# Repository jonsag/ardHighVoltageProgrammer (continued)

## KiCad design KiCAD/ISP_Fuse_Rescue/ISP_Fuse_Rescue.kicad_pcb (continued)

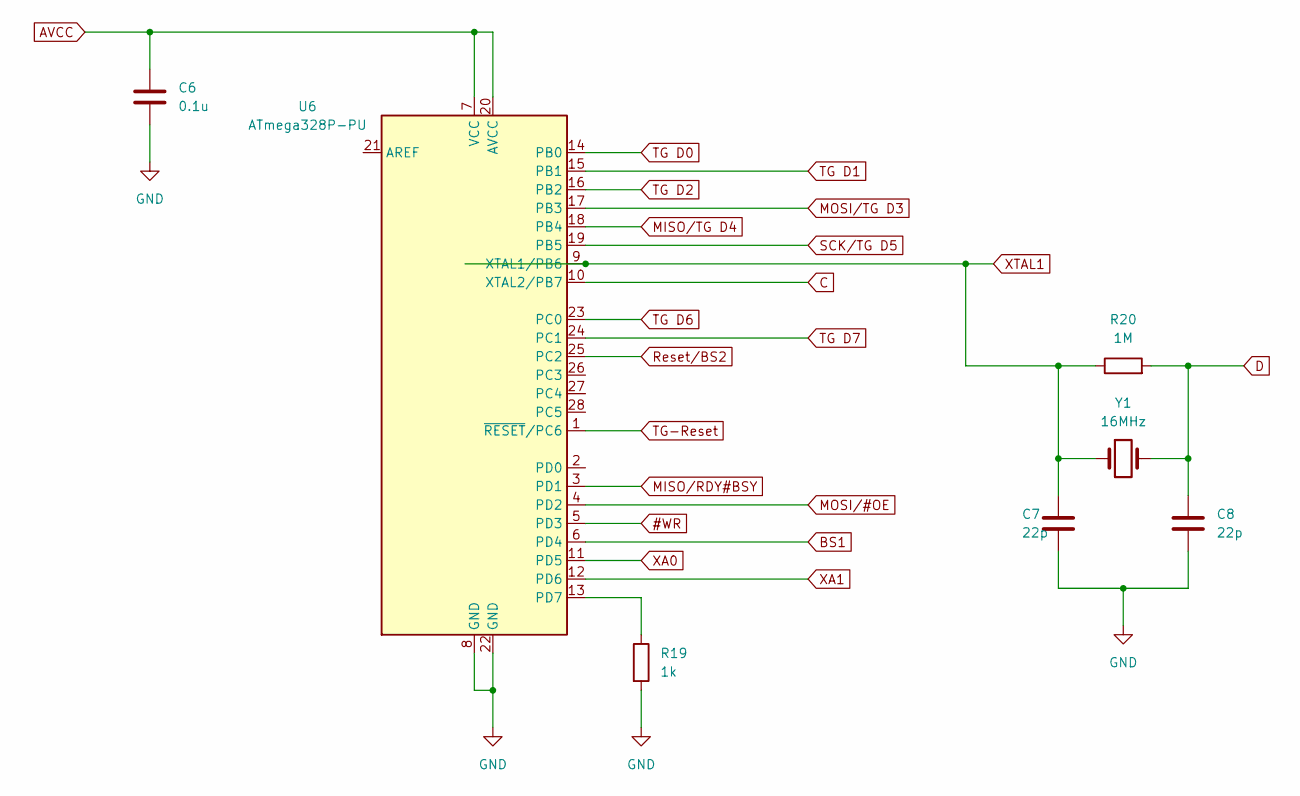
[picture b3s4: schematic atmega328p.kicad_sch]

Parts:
C6: 0.1u; CP_Radial_D5.0mm_P2.50mm_larger_pads
C7, C8: 22p; C_Disc_D3.0mm_W1.6mm_P2.50mm_larg
R19: 1k; R_Axial_DIN0207_L6.3mm_D2.5mm_P10.16mm_Horizontal_large
R20: 1M; R_Axial_DIN0207_L6.3mm_D2.5mm_P10.16mm_Horizontal_large
U6: ATmega328P-PU; ZIF_DIP_Socket-28_W6.9_W7.62_W7.62_W12.7_W13.5_large
Y1: 16MHz; Crystal_HC49-4H_Vertical_large

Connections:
#WR: U6.5 (PD3); also elsewhere on the board
AVCC: C6.1, U6.7 (VCC), U6.20 (AVCC); also elsewhere on the board
BS1: U6.6 (PD4); also elsewhere on the board
C: U6.10 (XTAL2/PB7); also elsewhere on the board
D: C8.1, R20.2, Y1.2; also elsewhere on the board
GND: C6.2, C7.2, C8.2, R19.2, U6.8 (GND), U6.22 (GND); also elsewhere on the board
MISO/RDY#BSY: U6.3 (PD1); also elsewhere on the board
MISO/TG D4: U6.18 (PB4); also elsewhere on the board
MOSI/#OE: U6.4 (PD2); also elsewhere on the board
MOSI/TG D3: U6.17 (PB3); also elsewhere on the board
unnamed: R19.1, U6.13 (PD7)
Reset/BS2: U6.25 (PC2); also elsewhere on the board
SCK/TG D5: U6.19 (PB5); also elsewhere on the board
TG D0: U6.14 (PB0); also elsewhere on the board
TG D1: U6.15 (PB1); also elsewhere on the board
TG D2: U6.16 (PB2); also elsewhere on the board
TG D6: U6.23 (PC0); also elsewhere on the board
TG D7: U6.24 (PC1); also elsewhere on the board
TG-Reset: U6.1 (~RESET/PC6); also elsewhere on the board
XA0: U6.11 (PD5)
XA1: U6.12 (PD6); also elsewhere on the board
XTAL1: C7.1, R20.1, U6.9 (XTAL1/PB6), Y1.1; also elsewhere on the board

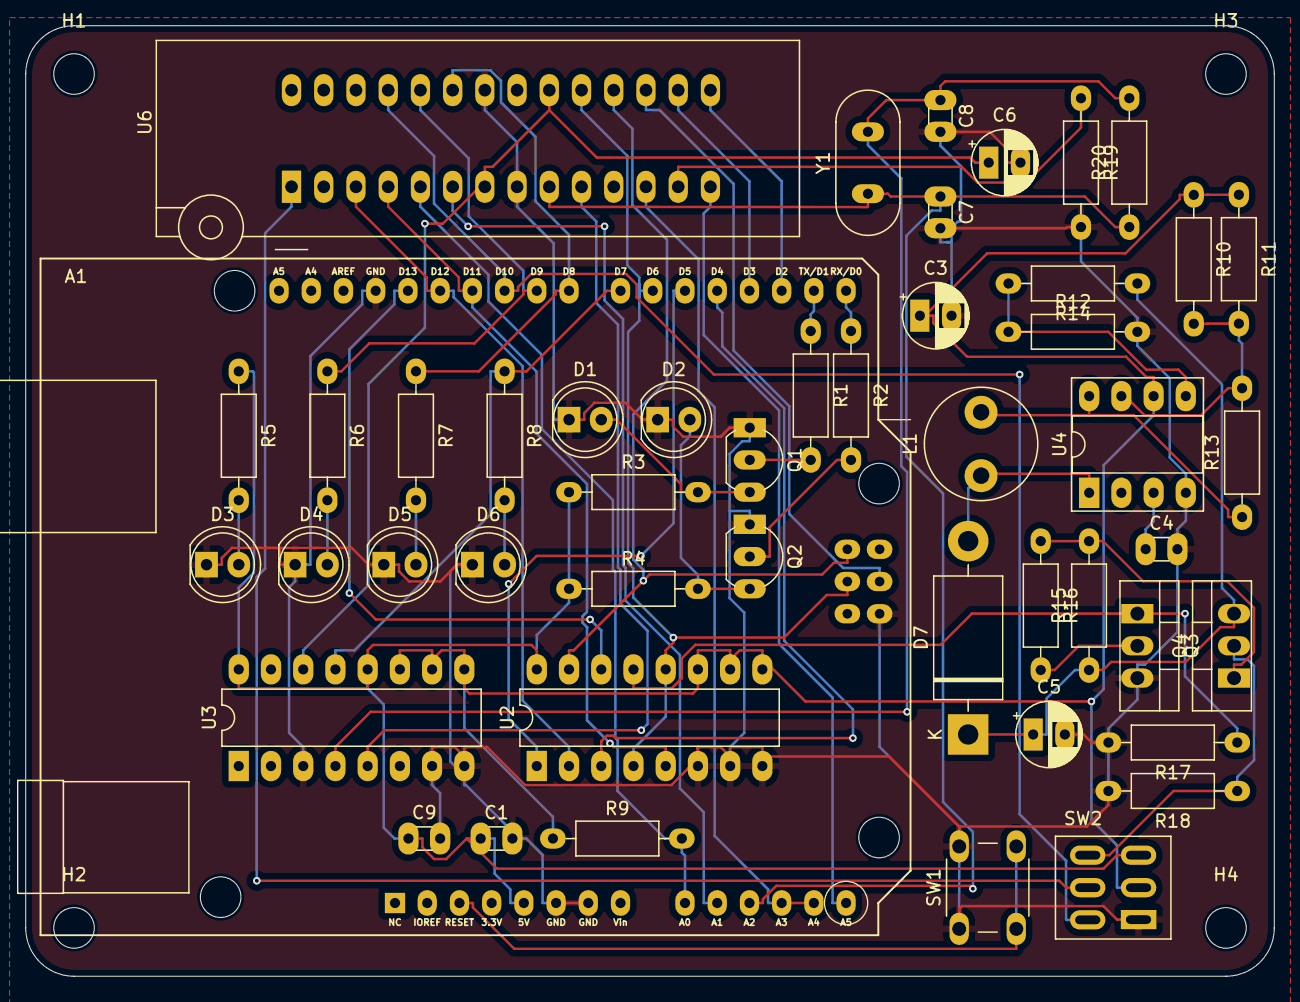
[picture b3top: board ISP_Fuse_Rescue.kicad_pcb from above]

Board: 2 copper layers, 98.4 x 74.9 mm, 52 parts (0 on the bottom side), 48 nets.

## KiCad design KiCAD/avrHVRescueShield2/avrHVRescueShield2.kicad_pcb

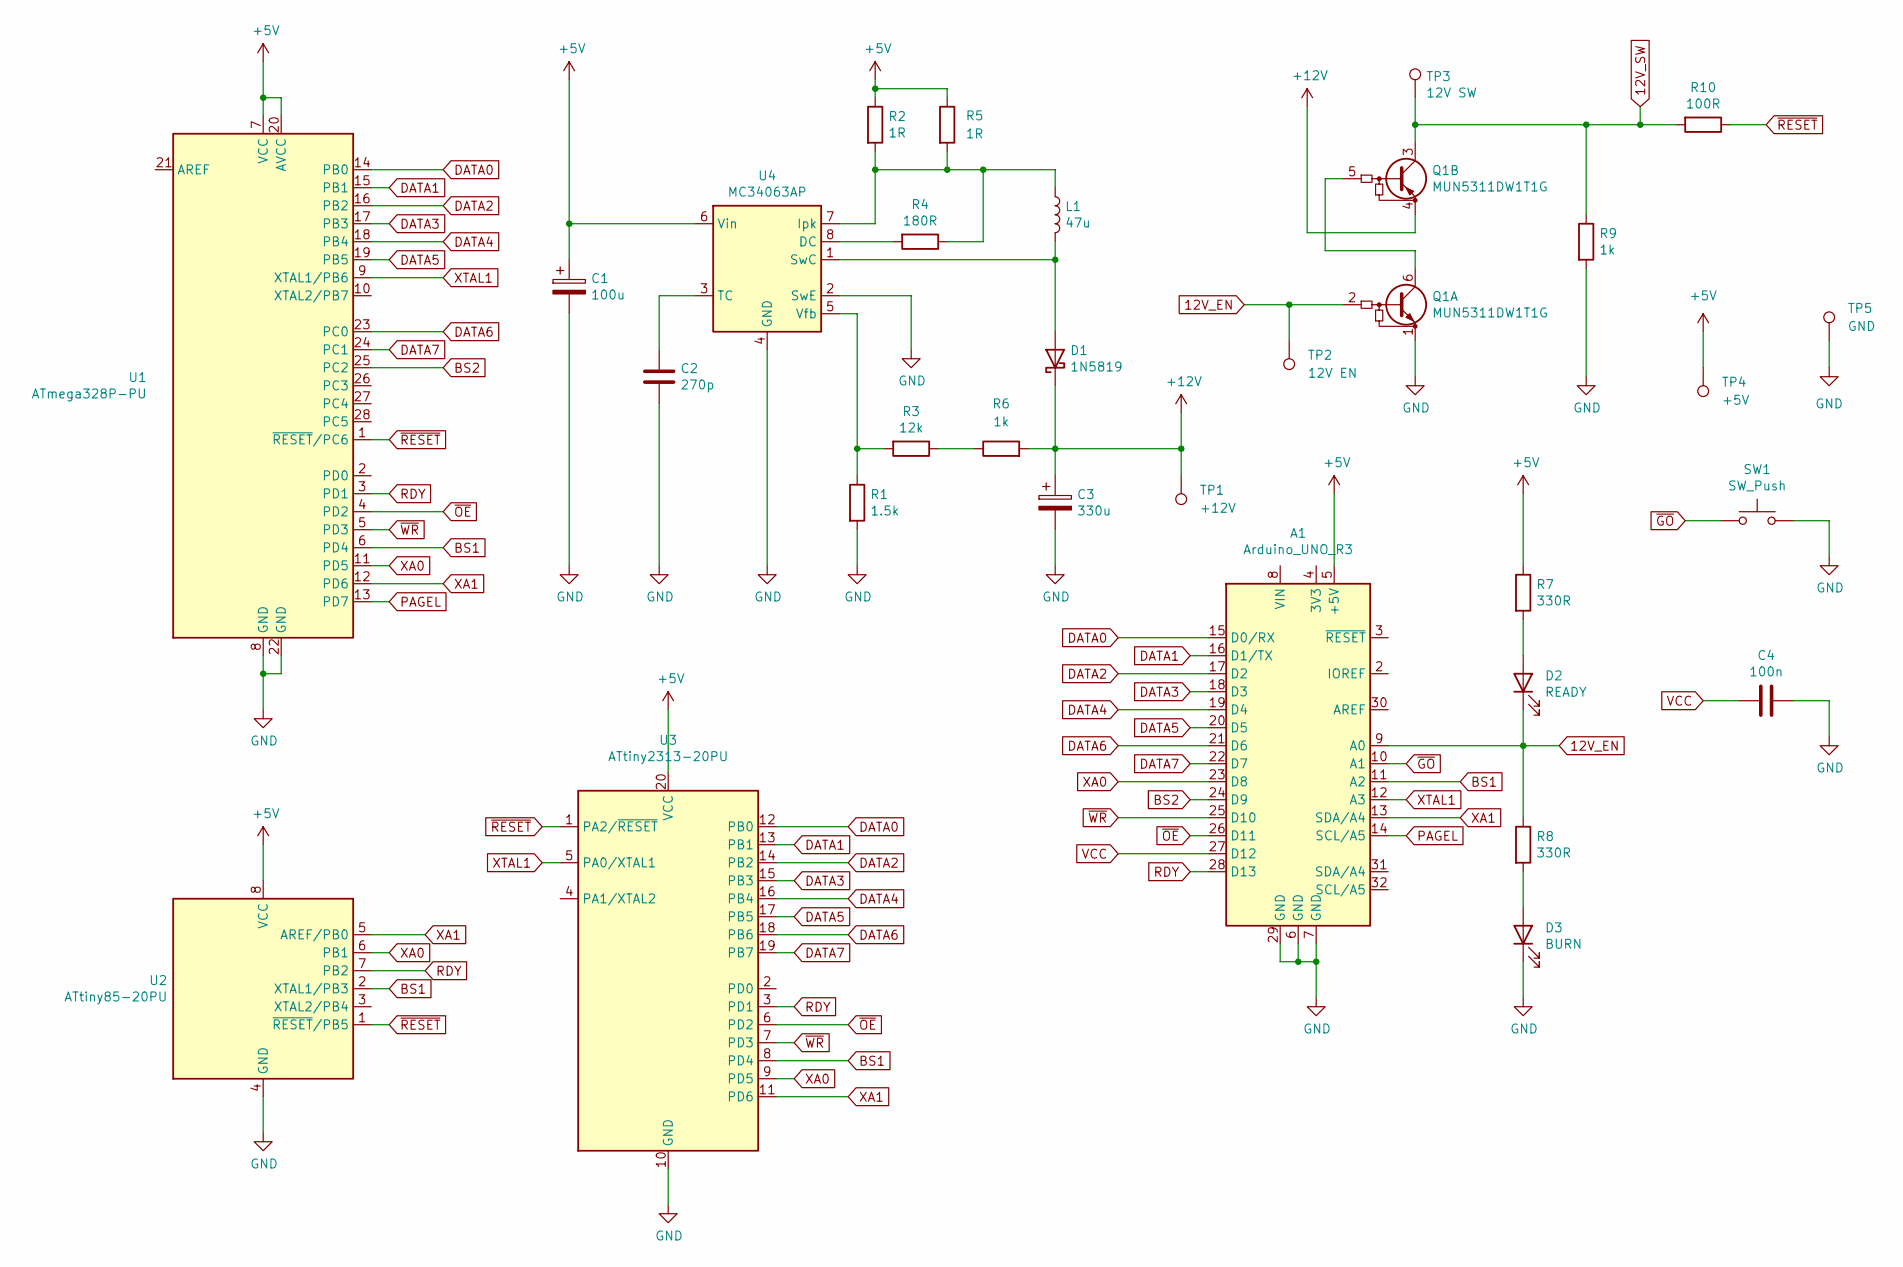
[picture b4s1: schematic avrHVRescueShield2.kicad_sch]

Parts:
A1: Arduino_UNO_R3; Arduino_UNO_R3_shield_large
C1: 100u; CP_Radial_D5.0mm_P2.50mm_larger_pads
C2: 270p; C_Disc_D3.0mm_W1.6mm_P2.50mm_larg
C3: 330u; CP_Radial_D10.0mm_P5.00mm_larger
C4: 100n; C_Disc_D3.0mm_W1.6mm_P2.50mm_larg
D1: 1N5819; D_DO-35_SOD27_P7.62mm_Horizontal_large
D2: READY; LED_D5.0mm_larger_pads
D3: BURN; LED_D5.0mm_larger_pads
L1: 47u; L_Axial_L9.5mm_D4.0mm_P12.70mm_Horizontal_Fastron_SMCC_large
Q1: MUN5311DW1T1G; SOT-363_SC-70-6_Handsoldering
R1: 1.5k; R_Axial_DIN0207_L6.3mm_D2.5mm_P10.16mm_Horizontal_large
R2, R5: 1R; R_Axial_DIN0207_L6.3mm_D2.5mm_P10.16mm_Horizontal_large
R3: 12k; R_Axial_DIN0207_L6.3mm_D2.5mm_P10.16mm_Horizontal_large
R4: 180R; R_Axial_DIN0207_L6.3mm_D2.5mm_P10.16mm_Horizontal_large
R6, R9: 1k; R_Axial_DIN0207_L6.3mm_D2.5mm_P10.16mm_Horizontal_large
R7, R8: 330R; R_Axial_DIN0207_L6.3mm_D2.5mm_P10.16mm_Horizontal_large
R10: 100R; R_Axial_DIN0207_L6.3mm_D2.5mm_P10.16mm_Horizontal_large
SW1: SW_Push; SW_PUSH_6mm_large
TP1: +12V; Single_solder_pad
TP2: 12V EN; Single_solder_pad
TP3: 12V SW; Single_solder_pad
TP4: +5V; Single_solder_pad
TP5: GND; Single_solder_pad
U1: ATmega328P-PU; ZIF_DIP_Socket-28_W6.9_W7.62_W7.62_W12.7_W13.5_large
U2: ATtiny85-20PU; DIP-8_W7.62mm_Socket_LongPads
U3: ATtiny2313-20PU; ZIF_DIP_Socket-20_W4.3_W5.08_W7.62_W10.16_W10.9_3M_220-3342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
U4: MC34063AP; DIP-8_W7.62mm_Socket_w_dip_packet_LongPads

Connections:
12V_EN: A1.9 (A0), D2.1 (K), Q1.2 (B1), R8.1, TP2.1
12V_SW: Q1.3 (C1), R9.1, R10.2, TP3.1
+5V: A1.5 (+5V), C1.1, R2.1, R5.1, R7.1, TP4.1, U1.7 (VCC), U1.20 (AVCC), U2.8 (VCC), U3.20 (VCC), U4.6 (Vin)
+12V: C3.1, D1.1 (K), Q1.4 (E1), R6.2, TP1.1
BS1: A1.11 (A2), U1.6 (PD4), U2.2 (XTAL1/PB3), U3.8 (PD4)
BS2: A1.24 (D9), U1.25 (PC2)
DATA0: A1.15 (D0/RX), U1.14 (PB0), U3.12 (PB0)
DATA1: A1.16 (D1/TX), U1.15 (PB1), U3.13 (PB1)
DATA2: A1.17 (D2), U1.16 (PB2), U3.14 (PB2)
DATA3: A1.18 (D3), U1.17 (PB3), U3.15 (PB3)
DATA4: A1.19 (D4), U1.18 (PB4), U3.16 (PB4)
DATA5: A1.20 (D5), U1.19 (PB5), U3.17 (PB5)
DATA6: A1.21 (D6), U1.23 (PC0), U3.18 (PB6)
DATA7: A1.22 (D7), U1.24 (PC1), U3.19 (PB7)
GND: A1.6 (GND), A1.7 (GND), A1.29 (GND), C1.2, C2.2, C3.2, C4.1, D3.1 (K), Q1.1 (E1), R1.2, R9.2, SW1.2, TP5.1, U1.8 (GND), U1.22 (GND), U2.4 (GND), U3.10 (GND), U4.2 (SwE), U4.4 (GND)
unnamed: C2.1, U4.3 (TC)
unnamed: D1.2 (A), L1.2, U4.1 (SwC)
unnamed: D2.2 (A), R7.2
unnamed: D3.2 (A), R8.2
unnamed: L1.1, R2.2, R4.1, R5.2, U4.7 (Ipk)
unnamed: Q1.5 (B1), Q1.6 (C1)
unnamed: R1.1, R3.2, U4.5 (Vfb)
unnamed: R3.1, R6.1
unnamed: R4.2, U4.8 (DC)
PAGEL: A1.14 (SCL/A5), U1.13 (PD7)
RDY: A1.28 (D13), U1.3 (PD1), U2.7 (PB2), U3.3 (PD1)
VCC: A1.27 (D12), C4.2
XA0: A1.23 (D8), U1.11 (PD5), U2.6 (PB1), U3.9 (PD5)
XA1: A1.13 (SDA/A4), U1.12 (PD6), U2.5 (AREF/PB0), U3.11 (PD6)
XTAL1: A1.12 (A3), U1.9 (XTAL1/PB6), U3.5 (PA0/XTAL1)
~GO: A1.10 (A1), SW1.1
~OE: A1.26 (D11), U1.4 (PD2), U3.6 (PD2)
~RESET: R10.1, U1.1 (~RESET/PC6), U2.1 (~RESET/PB5), U3.1 (PA2/~RESET)
~WR: A1.25 (D10), U1.5 (PD3), U3.7 (PD3)

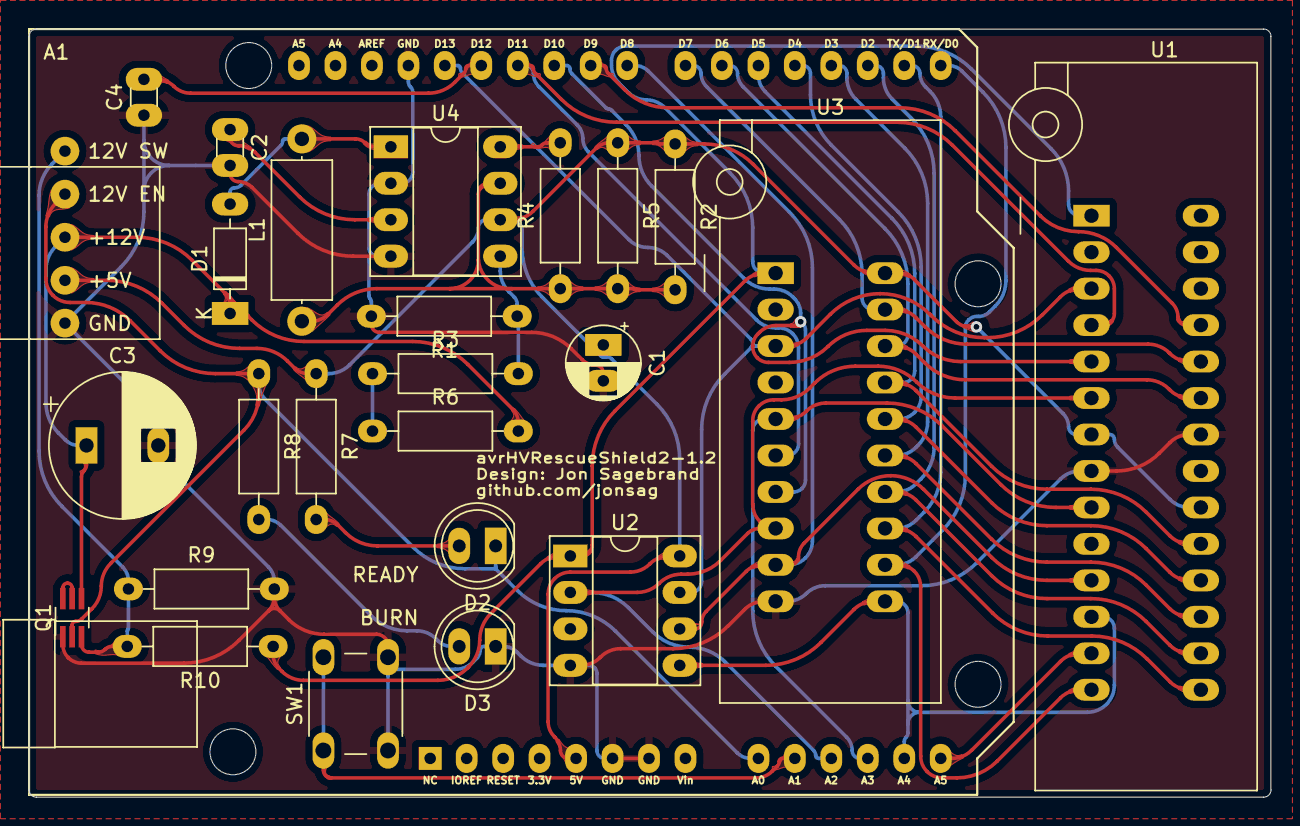
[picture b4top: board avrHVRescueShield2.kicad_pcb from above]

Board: 2 copper layers, 86.5 x 53.5 mm, 30 parts (0 on the bottom side), 34 nets.

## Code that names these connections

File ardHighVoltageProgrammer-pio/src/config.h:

#include <Arduino.h>

// User defined settings
#define DEFAULTMODE ATMEGA // If running in non-interactive mode, you need to set this to ATMEGA, TINY2313, or HVSP.
#define INTERACTIVE 1      // Set this to 0 to disable interactive mode
#define BURN_EFUSE 1       // Set this to 1 to enable burning extended fuse byte
#define BAUD 115200        // Serial port rate at which to talk to PC
#define SERIALTIMEOUT 3000 // Amount of time to wait for complete input if CR/LF off

// If interactive mode is off, these fuse settings are used instead of user prompted values
#define LFUSE 0x62 // default for ATmega328P per datasheet p282-284 0x62 UNO=0xFF
#define HFUSE 0xD9 // default for ATmega328P per datasheet p282-284 0xD9 UNO=0xDE Duemilanove328=0xDA
#define EFUSE 0xFF // default for ATmega328P per datasheet p282-284 0xFF UNO=0x05(effective FD)
// default low fuse  for ATtiny85 per datasheet p148-149 0x62 digispark=0xF1
// default high fuse for ATtiny85 per datasheet p148-149 0xDF digispark=0xD5
// default ext fuse  for ATtiny85 per datasheet p148-149 0xFF digispark=0xFE
// default low fuse  for ATtiny2313 per datasheet p159-160 0x64
// default high fuse for ATtiny2313 per datasheet p159-160 0xDF
// default ext fuse  for ATtiny2313 per datasheet p159-160 0xFF

// Pin Assignments
#define DATA0 A1
#define DATA1 1
#define DATA2 2
#define DATA3 3
#define DATA4 4
#define DATA5 5
#define DATA6 6
#define DATA7 7
#define VCC 12
#define RDY 13 // RDY/!BSY signal from target
#define OE 11
#define WR 10
#define BS1 A2
#define XA0 8
#define XA1 A4
#define RST A0 // 12V to target reset enable (!12V_EN)
#define XTAL1 A3
#define PAGELM A5
#define BS2M 9

// Pin assignment adjustments for Tiny
#define PAGELT BS1 // PAGEL is set to same pin as BS1 for ATtiny2313
#define BS2T XA1   // BS2 is set to same pin as XA1 for ATtiny2313
// Pin assignments for HVSP mode
#define SCI BS1
#define SDO RDY
#define SII XA0
#define SDI XA1

// Serial instructions for HVSP mode
// Based on the ATtiny85 datasheet Table 20-16 pg. 163-165.
// These instructions don't contain the necessary zero padding, which is added later.

// LFUSE
#define HVSP_READ_LFUSE_DATA B00000100   // For the commands we are interested in
#define HVSP_READ_LFUSE_INSTR1 B01001100 // only the 1st instruction contains a fixed data packet.
#define HVSP_READ_LFUSE_INSTR2 B01101000 // Instructions 2-3 have data = all zeros.
#define HVSP_READ_LFUSE_INSTR3 B01101100

#define HVSP_WRITE_LFUSE_DATA B01000000   // For the write instructions, the data contents
#define HVSP_WRITE_LFUSE_INSTR1 B01001100 // for instruction 2 are the desired fuse bits.
#define HVSP_WRITE_LFUSE_INSTR2 B00101100 // Instructions 3-4 have data = all zeros.
#define HVSP_WRITE_LFUSE_INSTR3 B01100100
#define HVSP_WRITE_LFUSE_INSTR4 B01101100

// HFUSE
#define HVSP_READ_HFUSE_DATA B00000100
#define HVSP_READ_HFUSE_INSTR1 B01001100
#define HVSP_READ_HFUSE_INSTR2 B01111010
#define HVSP_READ_HFUSE_INSTR3 B01111110

#define HVSP_WRITE_HFUSE_DATA B01000000
#define HVSP_WRITE_HFUSE_INSTR1 B01001100
#define HVSP_WRITE_HFUSE_INSTR2 B00101100
#define HVSP_WRITE_HFUSE_INSTR3 B01110100
#define HVSP_WRITE_HFUSE_INSTR4 B01111100

// EFUSE
// Note: not all ATtiny's have an EFUSE
#define HVSP_READ_EFUSE_DATA B00000100
#define HVSP_READ_EFUSE_INSTR1 B01001100
#define HVSP_READ_EFUSE_INSTR2 B01101010
#define HVSP_READ_EFUSE_INSTR3 B01101110

#define HVSP_WRITE_EFUSE_DATA B01000000
#define HVSP_WRITE_EFUSE_INSTR1 B01001100
#define HVSP_WRITE_EFUSE_INSTR2 B00101100
#define HVSP_WRITE_EFUSE_INSTR3 B01100110
#define HVSP_WRITE_EFUSE_INSTR4 B01101110

// Internal definitions
enum modelist
{
    ATMEGA,
    TINY2313,
    HVSP
};
enum fusesel
{
    LFUSE_SEL,
    HFUSE_SEL,
    EFUSE_SEL
};

// Global variables
byte mode = DEFAULTMODE;        // programming mode
String inputString = "";        // a string to hold incoming data
boolean stringComplete = false; // whether the string is complete
long val1;
byte base = 0;
byte lfuse = LFUSE;
byte hfuse = HFUSE;
byte efuse = EFUSE;

// These pin assignments change depending on which chip is being programmed,
// so they are put into variables
byte PAGEL = PAGELM;
byte BS2 = BS2M;

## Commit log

2021-09-22 Readme
2021-09-22 kicad start
2021-09-22 schematics
2021-09-22 sketch
2021-09-22 sketch converted to platformio
2021-09-24 Sketch and cad
2021-10-07 schematics n pcb
2021-10-08 readme schematics
2022-05-12 kicad6
2022-06-03 new pcb
2022-09-09 kicad
2022-09-28 readme and pio ini
2022-10-01 error in schematics
2022-10-01 minor pcb change
2023-02-21 kicad7
2025-01-12 renames
2025-01-15 ISP Fuse Rescue added
2025-01-23 ISP Fuse Rescue
2025-01-26 kicad new versionj
2025-01-26 isp fuse rescue smd
2025-01-26 smd fuse rescue
